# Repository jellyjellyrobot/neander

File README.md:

# Neander

The Neander is a microcontroller platform that is created for NUS Greyhats' X-CTF.

This board is based on the ESP8266 microcontroller series by Espressif and derives certain components from Adafruit's Feather and Sparkfun's Thing based on the same microcontroller platform.

## Specifications

- ESP8266 32 bit Microcontroller platform with Integrated 802.11 b/g/n
- Auto-Reset
- Deep Sleep option (enabled)
- 500mA 3.3V Voltage Regulator
- USB-Serial Interface (CP2102)
- 6 Buttons (including Reset)
- Lithium Polymer Charger
- Indicator LEDs (Charge, Power)
- Backlight LEDs and Switches

## Neander Accessory kit

The Neander comes with an accessory kit which includes the following

- Lithium Polymer Battery
- MicroUSB cable
- Short Lanyard (For CP2102)
- 10cm Dupont Jumper Cables (10 each: M-M, F-F, F-M)
- Single Row Headers 1*40 pin
- Double Row Headers 2*6 pin
- 6 Jumpers
- 2 Stickers

## Using the USB-Serial Adaptor

The on-board USB-Serial Adaptor is based on a Silabs CP2102 chip.

OS specific drivers can be found on the [manufacturer's website](http://www.silabs.com/products/mcu/Pages/USBtoUARTBridgeVCPDrivers.aspx). A tutorial on how to use this device can be found [here](https://learn.sparkfun.com/tutorials/cp2102-usb-to-serial-converter-hook-up-guide). The datasheet can be found [here](https://cdn.sparkfun.com/datasheets/BreakoutBoards/CP2102_v1.2.pdf).

## Interfacing with other electronics

The USB-Serial adaptor is supplied as a breakout board. If you need a serial adaptor "out in the field", you can choose to break it and solder on any 2.54mm compatible headers for convenience.

To interface the serial adaptor with other serial devices with the CP2102 in-situ, you may solder the double row headers found in the accessory packs and disconnect (desolder) all 5 SMD jumper pads.

## XCTF 2016

Here are the repositories for the [qualifiers] (https://github.com/NUSGreyhats/xctf-2016-quals-challenges) and [finals](https://github.com/NUSGreyhats/x-ctf-2016-finals).

## Contributors

Jacob  
Darell  
Yu Siang  
Jeremias

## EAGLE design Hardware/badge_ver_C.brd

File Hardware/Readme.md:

#Hardware

## Stages

This board was designed in 3 stages. 2 Prototypes were made (with mistakes :D) and the final board turned out pretty ok. Lucky us!

##Bill of Materials

The [Bill of Materials](https://docs.google.com/spreadsheets/d/1qAbk1U9EDFSMrGZ68tAHjeOSaGbgNGMX1J6-07fJV7c/edit?usp=sharing) can be found here!

## Production Writeups

Darell (@geekman) has produced a great writeup [here](http://irq5.io/2016/06/22/designing-the-x-ctf-2016-badge/)!

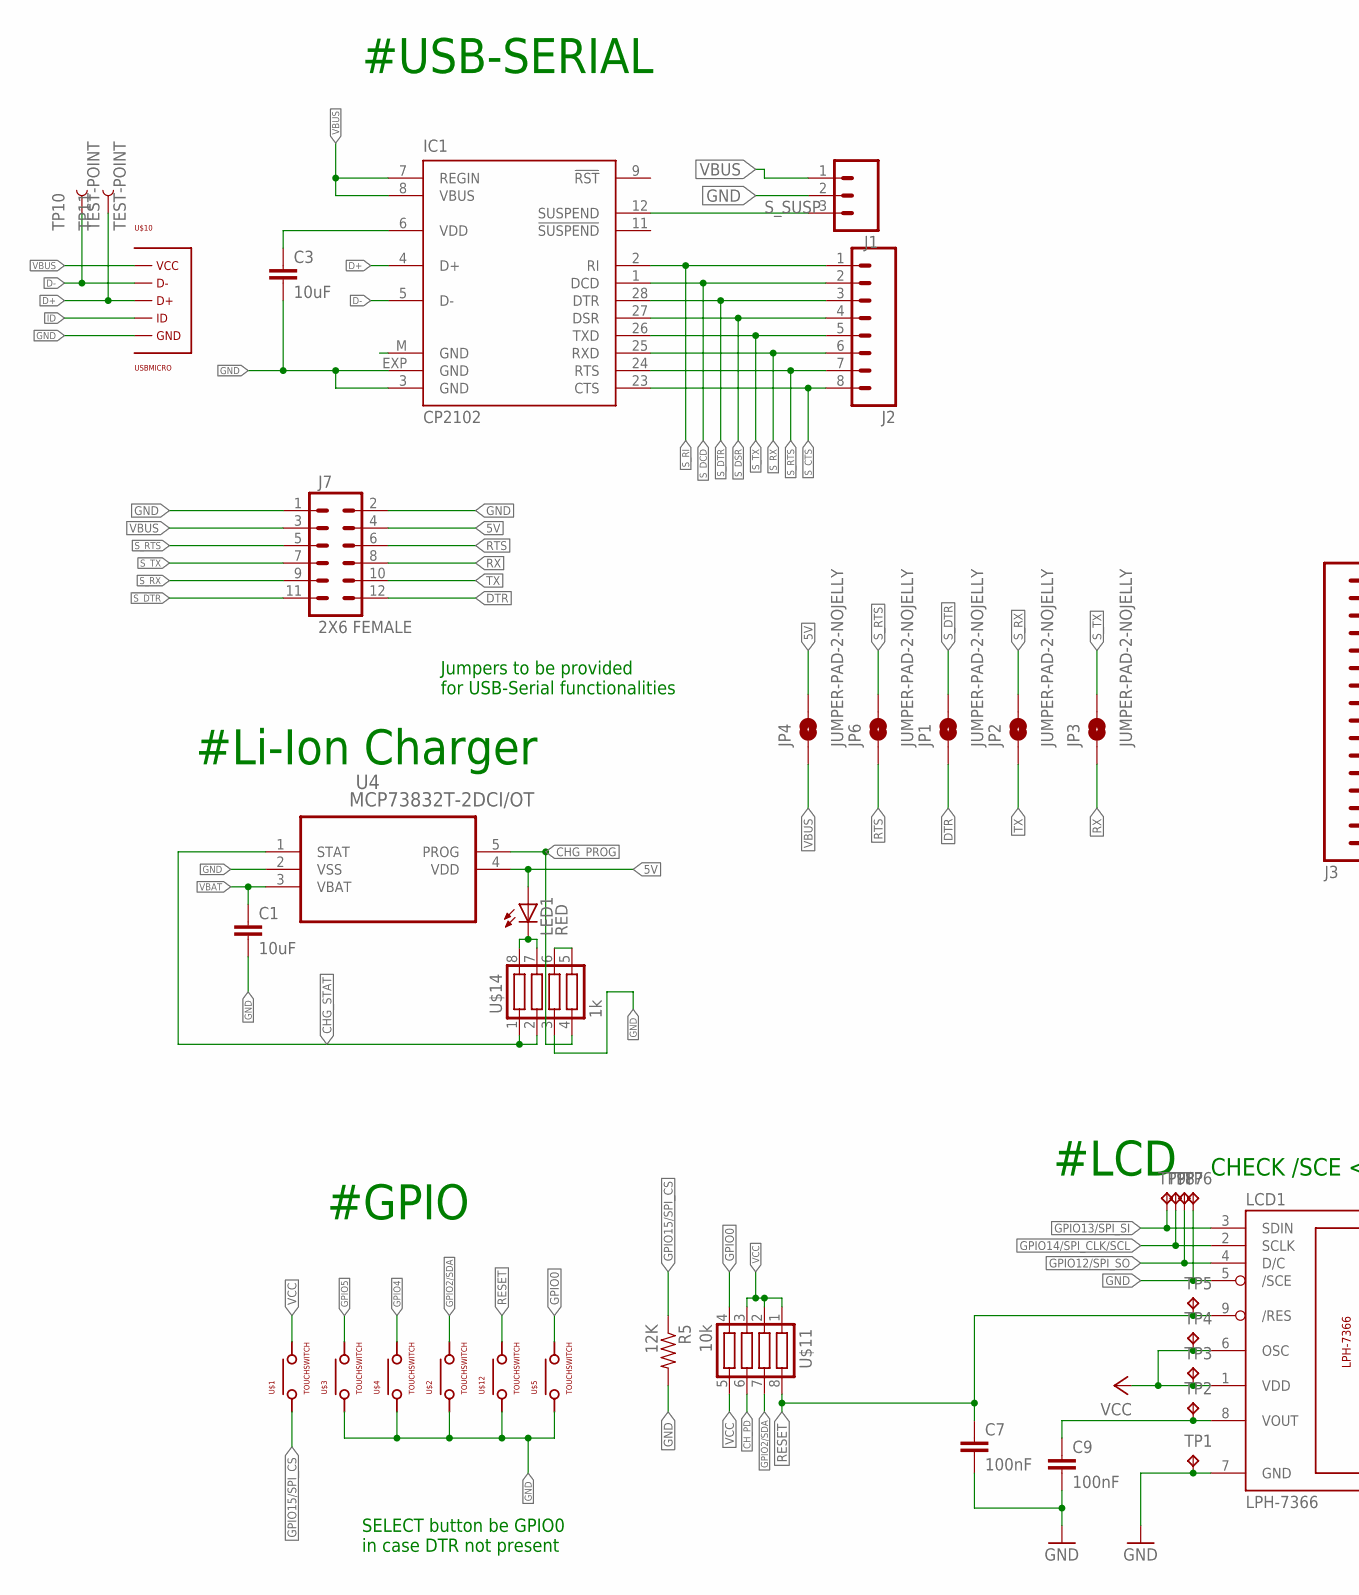
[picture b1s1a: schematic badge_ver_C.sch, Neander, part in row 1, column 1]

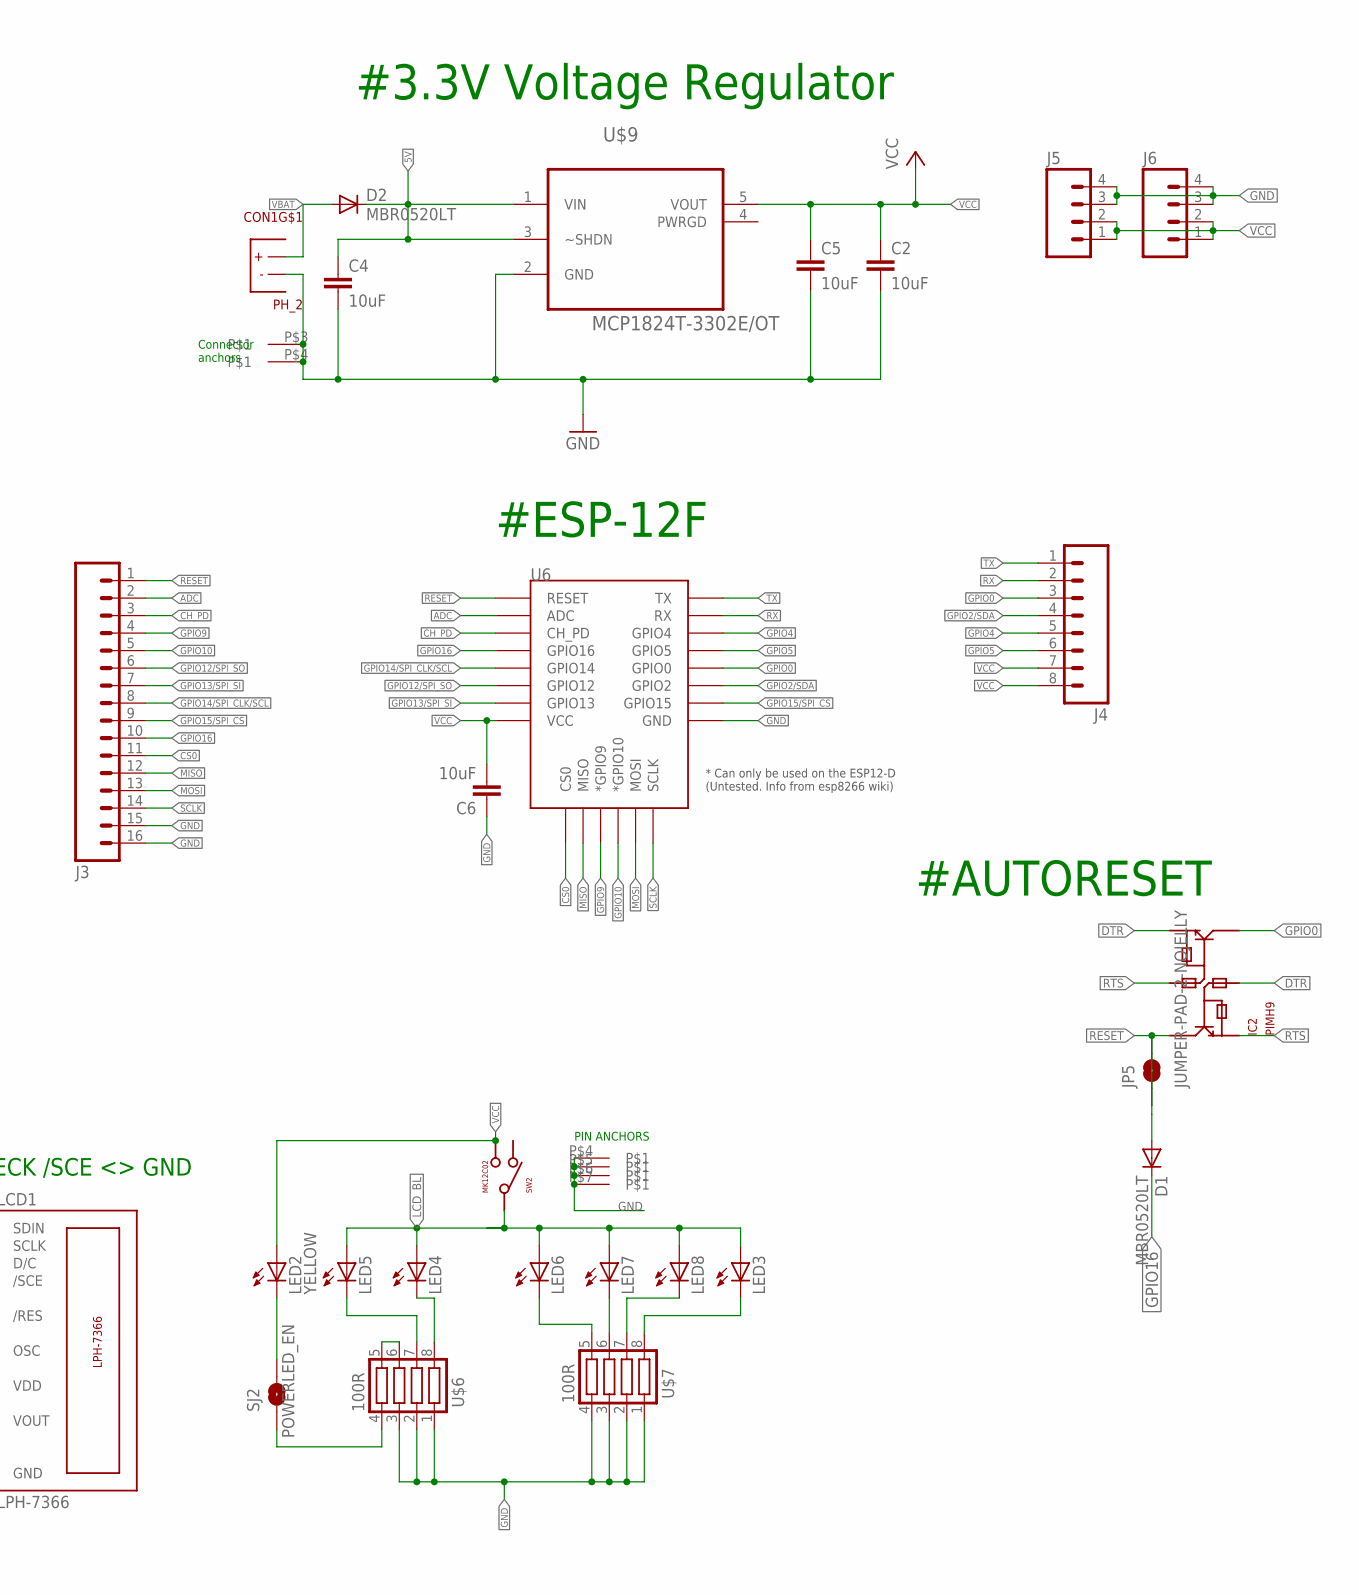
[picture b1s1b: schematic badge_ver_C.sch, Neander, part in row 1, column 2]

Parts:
C1, C2, C3, C4, C5, C6: 10uF; 0805-CAP
C7, C9: 100nF; 0805-CAP
CON1: PH_2
D1, D2: MBR0520LT; SOD123
IC1: CP2102; MLP28
IC2: PIMH9; SOT457
J1: M03PTH; 1X03
J2: M08SILK_FEMALE_PTH; 1X08
J3: M16PTH; 1X16
J4: M08; 1X08_ROUND
J5, J6: M04PTH; 1X04
J7: 2X6 FEMALE; 2X6
JP1, JP2, JP3, JP4, JP5, JP6: JUMPER-PAD-2-NOJELLY; JELLYPAD-JUMPER-2-NO_NO_SILK
LCD1: LPH-7366
LED1: RED; SML0805
LED2: YELLOW; SML0805
LED3, LED4, LED5, LED6, LED7, LED8: LEDSML0805; SML0805
R5: 12K; 0805
SJ2: POWERLED_EN; SJ_2S-TRACE
SW2: MK12C02
TP1, TP2, TP3, TP4, TP5, TP6, TP7, TP8, TP9: TPB1,27; B1,27
TP10, TP11: TEST-POINT; PAD.02X.02_JELLY
U4: MCP73832T-2DCI/OT; SOT95P300X145-5N
U6: ESP12ESMD; ESP12E-SMD
U$1, U$2, U$3, U$4, U$5, U$12: TOUCHSWITCH; EVQQWN03W
U$6, U$7: 100R; YC164
U$9: MCP1824T-3302E/OT; SOT95P270X145-5N
U$10: USBMICRO
U$11: 10k; YC164
U$14: 1k; YC164

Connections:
5V: C4.1, D2.C, J7.4, JP4.2, LED1.A, U4.4 (VDD), U$9.1 (VIN), U$9.3 (~SHDN)
ADC: J3.2, U6.ADC
CHG_PROG: U4.5 (PROG), U$14.4
CHG_STAT: U4.1 (STAT), U$14.1, U$14.2
CH_PD: J3.3, U6.CH_PD, U$11.6
CS0: J3.11, U6.CS0
D+: IC1.4 (D+), TP11.P$1, U$10.P$D+
D-: IC1.5 (D-), TP10.P$1, U$10.P$D-
DTR: IC2.P$2, IC2.P$4, J7.12, JP1.1
GND: C1.2, C2.2, C3.2, C4.2, C5.2, C6.1, C7.2, C9.2, CON1.P$1, CON1.P$3, CON1.P$4, IC1.3 (GND), IC1.EXP (GND), J1.2, J3.15, J3.16, J5.3, J5.4, J6.3, J6.4, J7.1, J7.2, LCD1.5 (/SCE), LCD1.7 (GND), R5.2, SW2.P$4, SW2.P$5, SW2.P$6, SW2.P$7, TP1.TP, TP6.TP, U4.2 (VSS), U6.GND, U$2.P$1, U$2.P$4, U$3.P$1, U$3.P$4, U$4.P$1, U$4.P$4, U$5.P$1, U$5.P$4, U$6.1, U$6.2, U$6.3, U$7.1, U$7.2, U$7.3, U$7.4, U$9.2 (GND), U$10.P$GND, U$12.P$1, U$12.P$4, U$14.3
GPIO0: IC2.P$3, J4.3, U6.GPIO0, U$5.P$2, U$5.P$3, U$11.4
GPIO2/SDA: J4.4, U6.GPIO2, U$2.P$2, U$2.P$3, U$11.7
GPIO4: J4.5, U6.GPIO4, U$4.P$2, U$4.P$3
GPIO5: J4.6, U6.GPIO5, U$3.P$2, U$3.P$3
GPIO9: J3.4, U6.GPIO9 (*GPIO9)
GPIO10: J3.5, U6.GPIO10 (*GPIO10)
GPIO12/SPI_SO: J3.6, LCD1.4 (D/C), TP7.TP, U6.GPIO12
GPIO13/SPI_SI: J3.7, LCD1.3 (SDIN), TP9.TP, U6.GPIO13
GPIO14/SPI_CLK/SCL: J3.8, LCD1.2 (SCLK), TP8.TP, U6.GPIO14
GPIO15/SPI_CS: J3.9, R5.1, U6.GPIO15, U$1.P$1, U$1.P$4
GPIO16: D1.C, J3.10, U6.GPIO16
ID: U$10.P$ID
LCD_BL: LED3.A, LED4.A, LED5.A, LED6.A, LED7.A, LED8.A, SW2.P$2
MISO: J3.12, U6.MISO
MOSI: J3.13, U6.MOSI
unnamed: LED1.C, U$14.7, U$14.8
unnamed: U$14.5, U$14.6
unnamed: LED7.C, U$7.6
unnamed: LED8.C, U$7.7
unnamed: C9.1, LCD1.8 (VOUT), TP2.TP
unnamed: U$6.5, U$6.6
unnamed: LED4.C, U$6.8
unnamed: LED5.C, U$6.7
unnamed: LED3.C, U$7.8
unnamed: SJ2.1, U$6.4
unnamed: LED2.C, SJ2.2
unnamed: C3.1, IC1.6 (VDD)
unnamed: LED6.C, U$7.5
RESET: C7.1, D1.A, IC2.P$6, J3.1, JP5.1, JP5.2, LCD1.9 (/RES), TP5.TP, U6.RESET, U$11.8, U$12.P$2, U$12.P$3
RTS: IC2.P$1, IC2.P$5, J7.6, JP6.1
RX: J4.2, J7.8, JP3.1, U6.RXD0 (RX)
SCLK: J3.14, U6.SCLK
S_CTS: IC1.23 (CTS), J2.8
S_DCD: IC1.1 (DCD), J2.2
S_DSR: IC1.27 (DSR), J2.4
S_DTR: IC1.28 (DTR), J2.3, J7.11, JP1.2
S_RI: IC1.2 (RI), J2.1
S_RTS: IC1.24 (RTS), J2.7, J7.5, JP6.2
S_RX: IC1.25 (RXD), J2.6, J7.9, JP2.2
S_SUSP: IC1.12 (SUSPEND), J1.3
S_TX: IC1.26 (TXD), J2.5, J7.7, JP3.2
TX: J4.1, J7.10, JP2.1, U6.TXD0 (TX)
VBAT: C1.1, CON1.P$2, D2.A, U4.3 (VBAT)
VBUS: IC1.7 (REGIN), IC1.8 (VBUS), J1.1, J7.3, JP4.1, U$10.P$VCC
VCC: C2.1, C5.1, C6.2, J4.7, J4.8, J5.1, J5.2, J6.1, J6.2, LCD1.1 (VDD), LCD1.6 (OSC), LED2.A, SW2.P$3, TP3.TP, TP4.TP, U6.VCC, U$1.P$2, U$1.P$3, U$9.5 (VOUT), U$11.1, U$11.2, U$11.3, U$11.5

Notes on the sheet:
SELECT button be GPIO0 in case DTR not present
#LCD
#Li-Ion Charger
#3.3V Voltage Regulator
#USB-SERIAL
#GPIO
#AUTORESET
#ESP-12F
Jumpers to be provided for USB-Serial functionalities
CHECK /SCE <> GND
Connector anchors
PIN ANCHORS

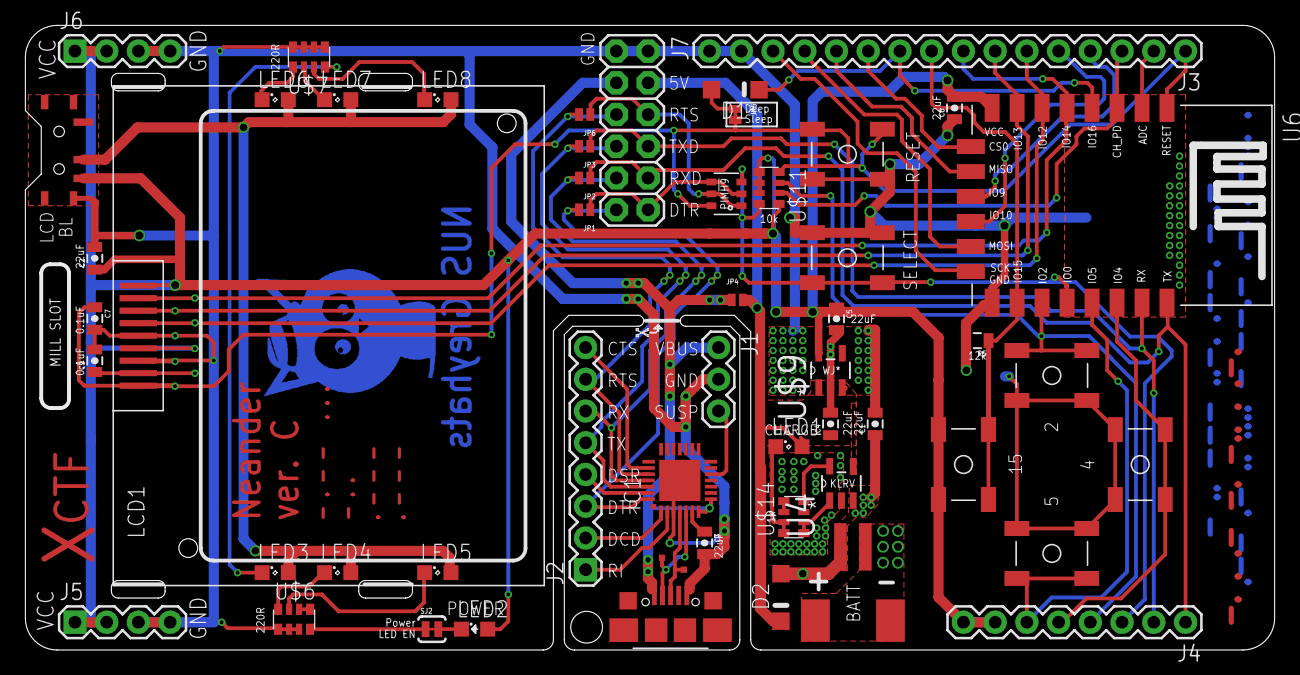
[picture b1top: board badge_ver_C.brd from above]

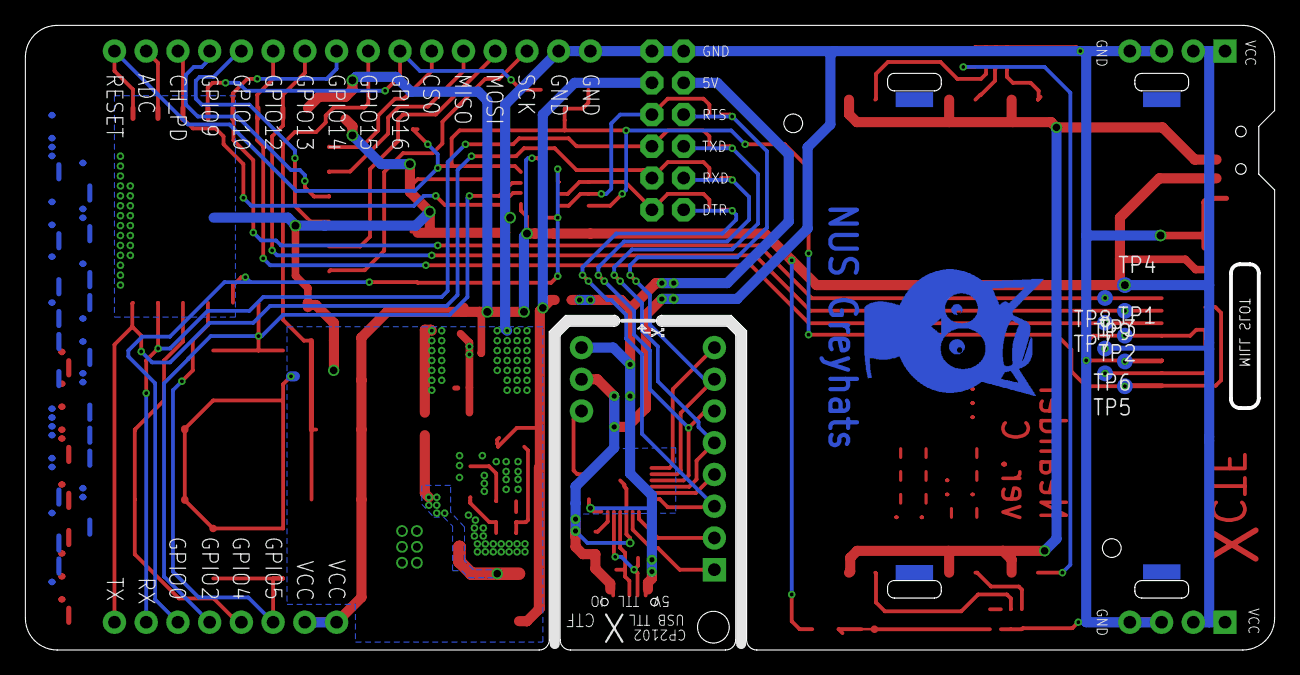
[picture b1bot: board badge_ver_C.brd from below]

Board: 2 copper layers, 99.8 x 49.8 mm, 63 parts (9 on the bottom side), 54 nets.

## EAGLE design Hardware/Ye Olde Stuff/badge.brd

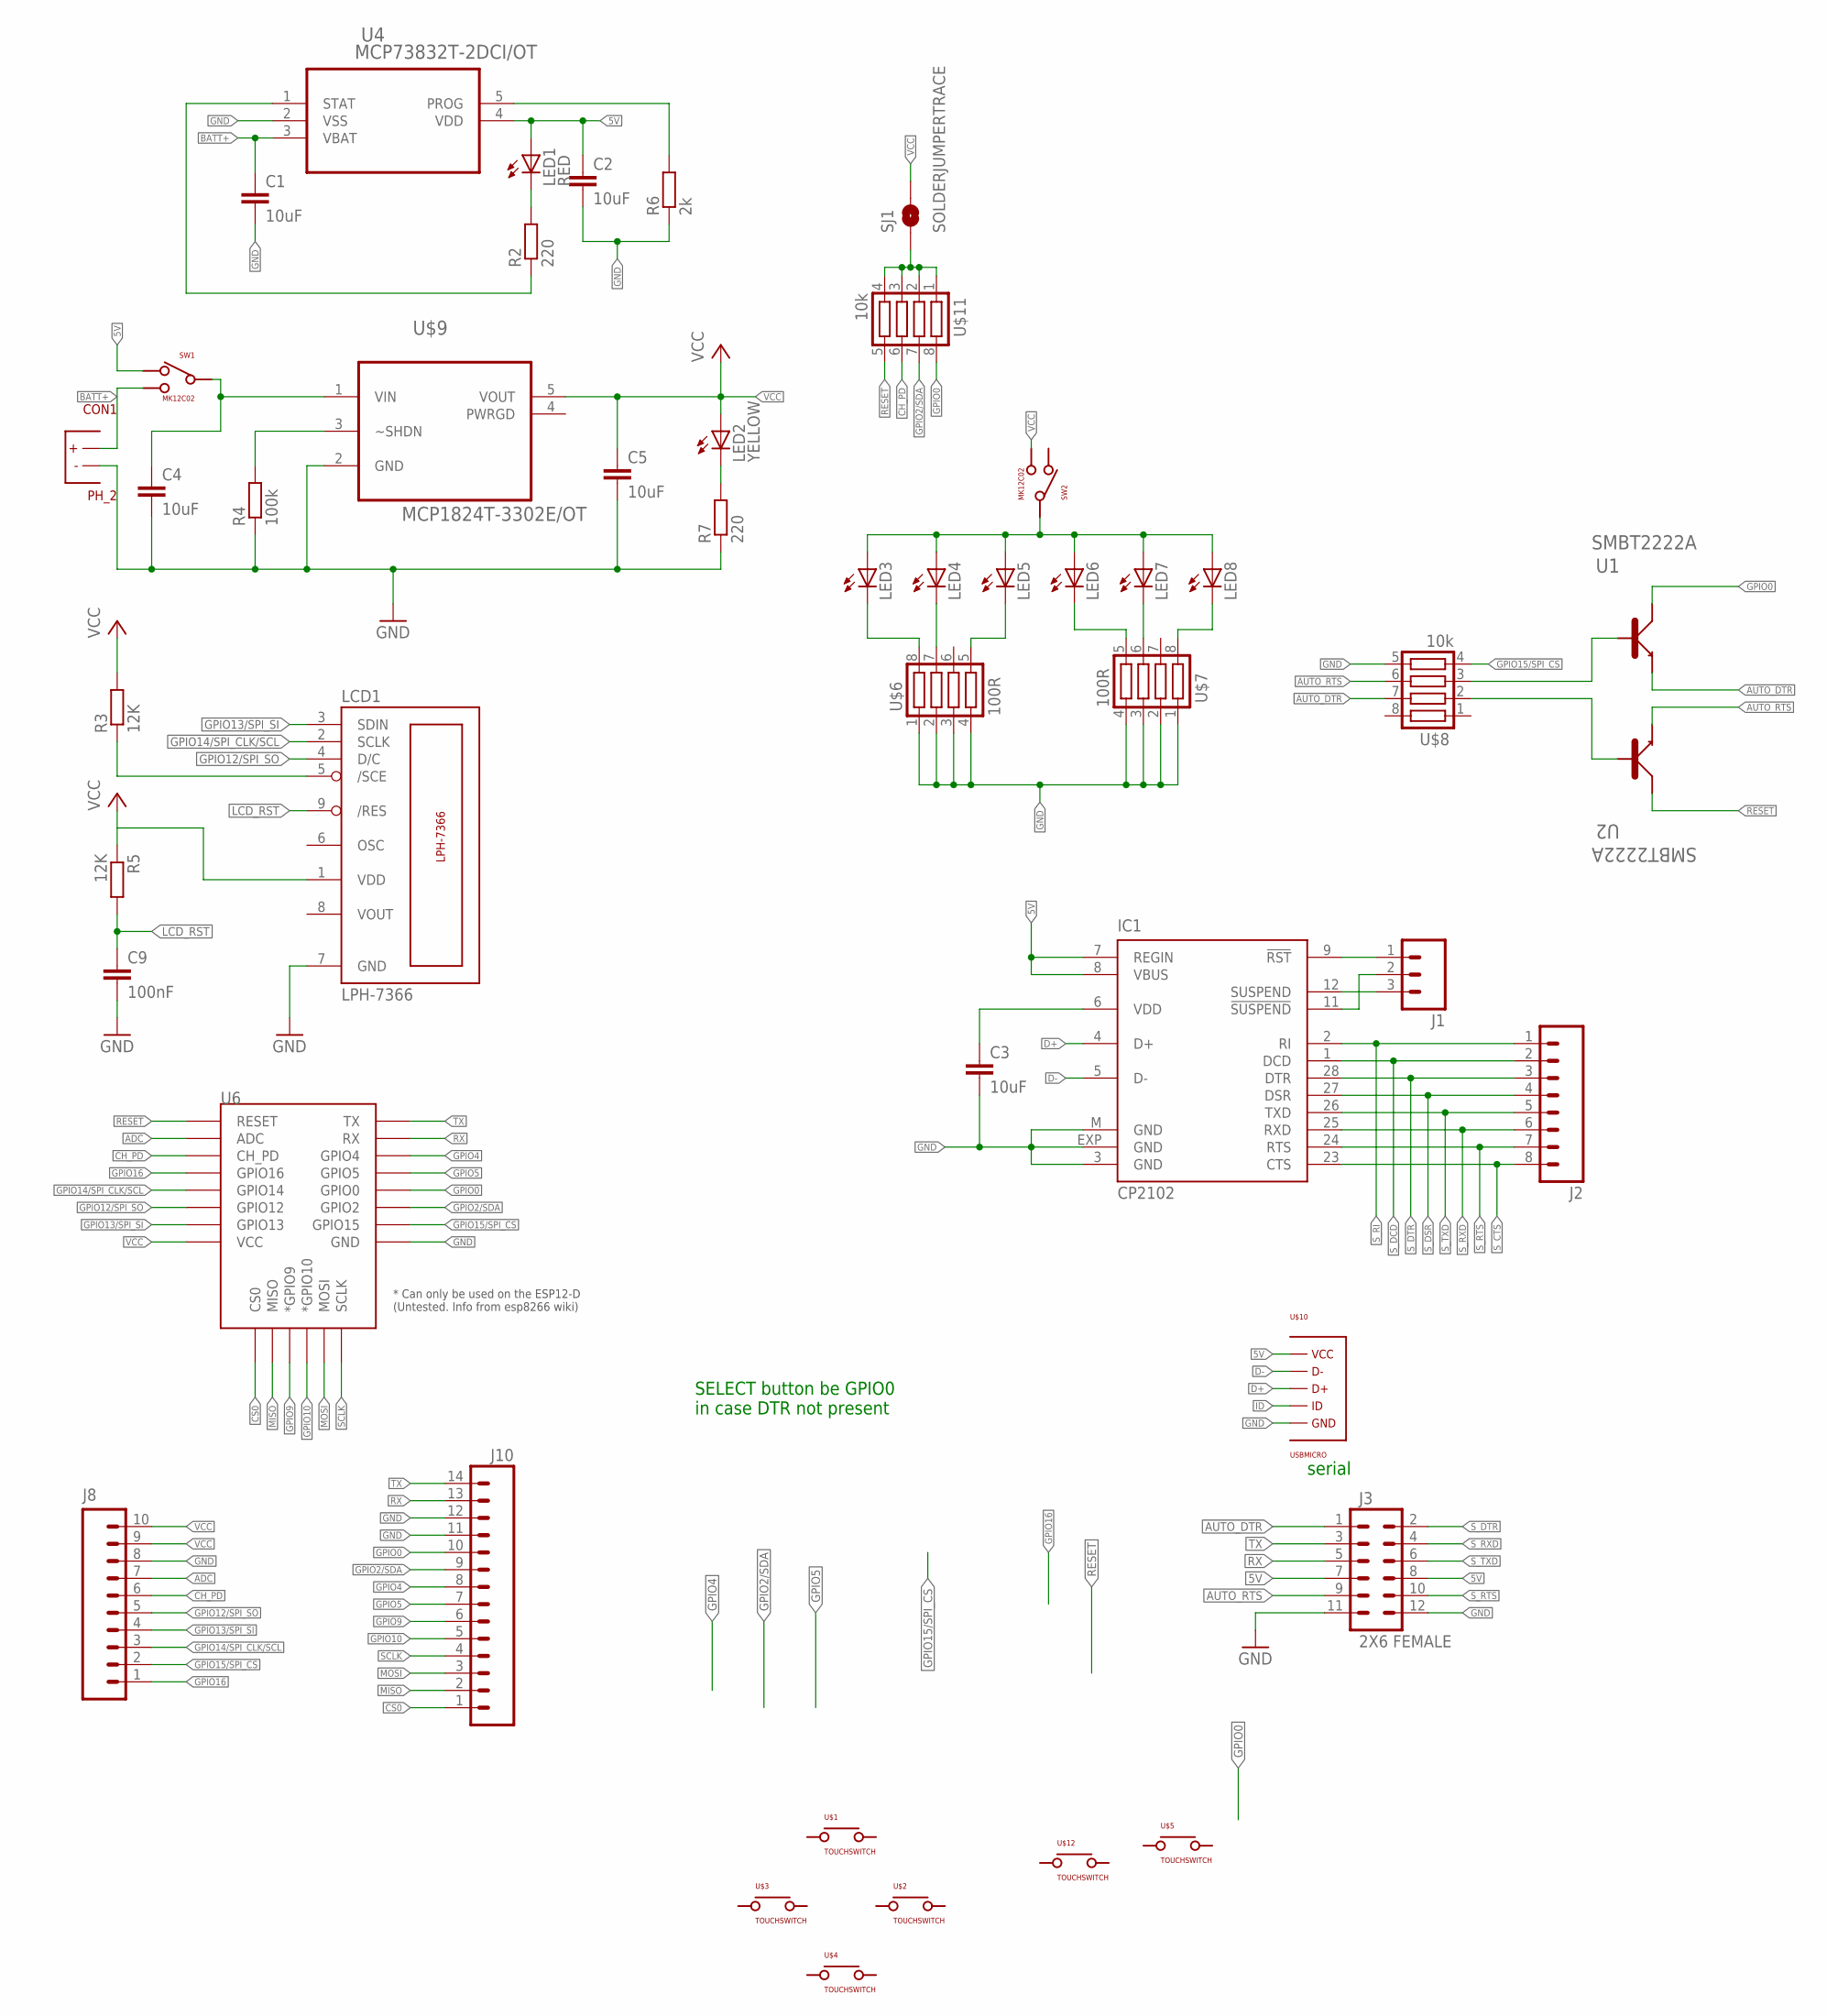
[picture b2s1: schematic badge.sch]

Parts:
C1, C2, C3, C4, C5: 10uF; C0603K
C9: 100nF; C0603K
CON1: PH_2
IC1: CP2102; MLP28
J1: M03PTH; 1X03
J2: M08SILK_FEMALE_PTH; 1X08
J3: 2X6 FEMALE; 2X6
J8: M10SILK_FEMALE_PTH; 1X10
J10: M14; 1X14
LCD1: LPH-7366
LED1: RED; SML0805
LED2: YELLOW; SML0805
LED3, LED4, LED5, LED6, LED7, LED8: LEDSML0805; SML0805
R2, R7: 220; R0603W
R3, R5: 12K; R0603W
R4: 100k; R0603W
R6: 2k; R0603W
SJ1: SOLDERJUMPERTRACE; SJ_2S-TRACE
SW1, SW2: MK12C02
U1, U2: SMBT2222A; SOT95P290X110-3N
U4: MCP73832T-2DCI/OT; SOT95P300X145-5N
U6: ESP12ESMD; ESP12E-SMD
U$1, U$2, U$3, U$4, U$5, U$12: TOUCHSWITCH; EVQQWN03W
U$6, U$7: 100R; YC164
U$8, U$11: 10k; YC164
U$9: MCP1824T-3302E/OT; SOT95P270X145-5N
U$10: USBMICRO

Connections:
5V: C2.1, IC1.7 (REGIN), IC1.8 (VBUS), J3.7, J3.8, LED1.A, SW1.P$2, U4.4 (VDD), U$10.P$VCC
ADC: J8.7, U6.ADC
AUTO_DTR: J3.1, U1.2 (E), U$8.7
AUTO_RTS: J3.9, U2.2 (E), U$8.6
BATT+: C1.1, CON1.P$2, SW1.P$3, U4.3 (VBAT)
CH_PD: J8.6, U6.CH_PD, U$11.6
CS0: J10.1, U6.CS0
D+: IC1.4 (D+), U$10.P$D+
D-: IC1.5 (D-), U$10.P$D-
GND: C1.2, C2.2, C3.2, C4.2, C5.2, C9.2, CON1.P$1, IC1.3 (GND), IC1.EXP (GND), IC1.M (GND), J3.11, J3.12, J8.8, J10.11, J10.12, LCD1.7 (GND), R4.1, R6.1, R7.1, U4.2 (VSS), U6.GND, U$6.1, U$6.2, U$6.3, U$6.4, U$7.1, U$7.2, U$7.3, U$7.4, U$8.5, U$9.2 (GND), U$10.P$GND
GPIO0: J10.10, U1.3 (C), U6.GPIO0, U$11.8
GPIO2/SDA: J10.9, U6.GPIO2, U$11.7
GPIO4: J10.8, U6.GPIO4
GPIO5: J10.7, U6.GPIO5
GPIO9: J10.6, U6.GPIO9 (*GPIO9)
GPIO10: J10.5, U6.GPIO10 (*GPIO10)
GPIO12/SPI_SO: J8.5, LCD1.4 (D/C), U6.GPIO12
GPIO13/SPI_SI: J8.4, LCD1.3 (SDIN), U6.GPIO13
GPIO14/SPI_CLK/SCL: J8.3, LCD1.2 (SCLK), U6.GPIO14
GPIO15/SPI_CS: J8.2, U6.GPIO15, U$8.4
GPIO16: J8.1, U6.GPIO16
ID: U$10.P$ID
LCD_RST: C9.1, LCD1.9 (/RES), R5.2
MISO: J10.2, U6.MISO
MOSI: J10.3, U6.MOSI
unnamed: C4.1, SW1.P$1, U$9.1 (VIN)
unnamed: LED3.A, LED4.A, LED5.A, LED6.A, LED7.A, LED8.A, SW2.P$1
unnamed: LCD1.5 (/SCE), R3.1
unnamed: R4.2, U$9.3 (~SHDN)
unnamed: SJ1.1, U$11.1, U$11.2, U$11.3, U$11.4
unnamed: R6.2, U4.5 (PROG)
unnamed: LED2.C, R7.2
unnamed: LED7.C, U$7.6
unnamed: LED1.C, R2.2
unnamed: R2.1, U4.1 (STAT)
unnamed: LED3.C, U$6.8
unnamed: LED4.C, U$6.7
unnamed: LED5.C, U$6.5
unnamed: U1.1 (B), U$8.3
unnamed: IC1.11 (!SUSPEND), J1.2
unnamed: IC1.12 (SUSPEND), J1.3
unnamed: U2.1 (B), U$8.2
unnamed: IC1.9 (!RST), J1.1
unnamed: C3.1, IC1.6 (VDD)
unnamed: LED6.C, U$7.5
unnamed: LED8.C, U$7.8
RESET: U2.3 (C), U6.RESET, U$11.5
RX: J3.5, J10.13, U6.RXD0 (RX)
SCLK: J10.4, U6.SCLK
S_CTS: IC1.23 (CTS), J2.8
S_DCD: IC1.1 (DCD), J2.2
S_DSR: IC1.27 (DSR), J2.4
S_DTR: IC1.28 (DTR), J2.3, J3.2
S_RI: IC1.2 (RI), J2.1
S_RTS: IC1.24 (RTS), J2.7, J3.10
S_RXD: IC1.25 (RXD), J2.6, J3.4
S_TXD: IC1.26 (TXD), J2.5, J3.6
TX: J3.3, J10.14, U6.TXD0 (TX)
VCC: C5.1, J8.9, J8.10, LCD1.1 (VDD), LED2.A, R3.2, R5.1, SJ1.2, SW2.P$3, U6.VCC, U$9.5 (VOUT)

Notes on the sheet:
serial
SELECT button be GPIO0 in case DTR not present

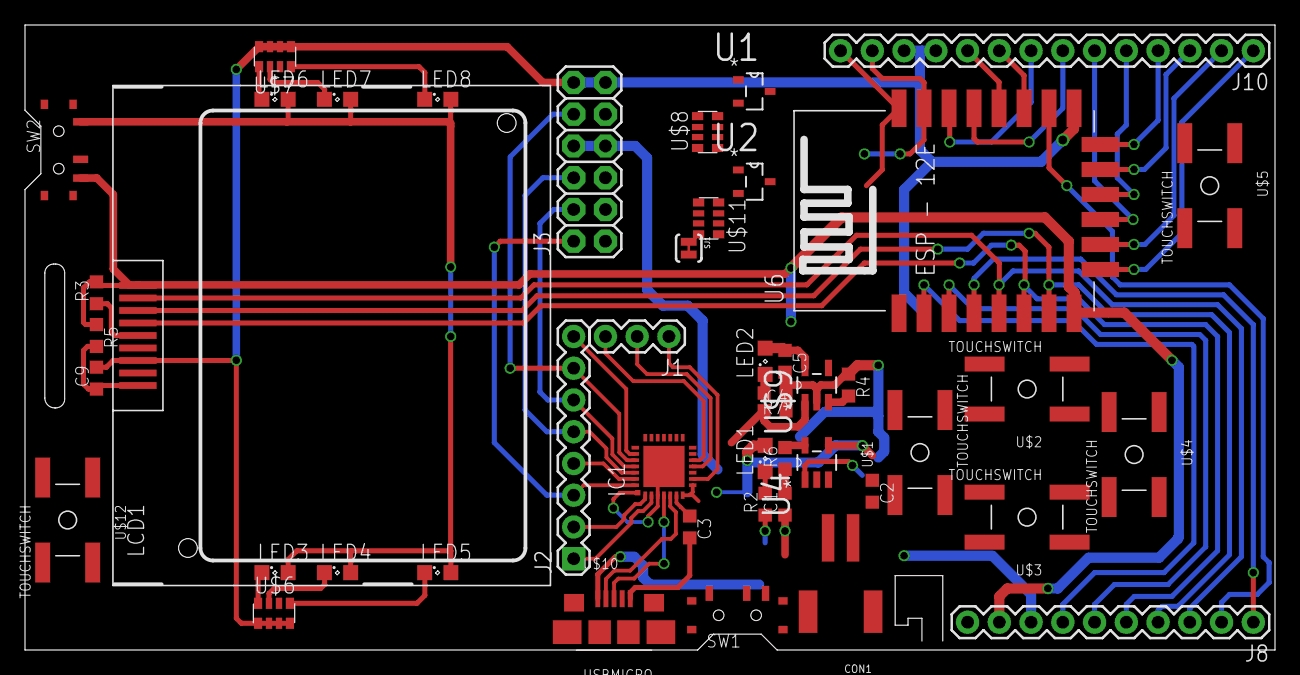
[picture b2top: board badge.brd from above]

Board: 2 copper layers, 100.0 x 50.0 mm, 47 parts (0 on the bottom side), 58 nets.

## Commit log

2016-03-10 init
2016-03-13 for ys
2016-03-18 switching over to ESP-12e/f
2016-03-21 before the big change
2016-03-22 before cp2102
2016-03-22 the change cometh
2016-03-23 before addition of autoreset
2016-03-24 Preliminary Neander v0.0
2016-03-24 changed readme
2016-03-24 forgot one name
2016-03-24 Schematic: LDO !shdn is to be high, not low
2016-03-25 Redid a lot of stuff, added silks.
2016-03-25 Fixed the files places
2016-03-25 Moved power LED, sharing the r-net for the backlight
2016-03-25 DTR and RTS silks on jumper header were swapped
2016-03-25 Swapped a silks, added more silks, bit of routing changes
2016-03-25 Moved a bit of stuff to prevent stop-mask errors, and one dimension error
2016-03-25 added some changes from YS
2016-03-25 Paralleled GND trace, rerouted reset trace for wider separation
2016-03-25 deleted lone component
2016-03-25 Fixed odd shaped reset trace at reset button
2016-03-25 Minimal nonessential changes
2016-03-26 moved res array U to away from RESET button
2016-03-26 rectified errors in ERC, DRC
2016-03-26 routed LED traces away from LCD mounting holes, prevent short between USB case and VBUS
2016-03-26 Added snapoffable USB-serial
2016-03-26 One cap's silk got mangled in the cut path
2016-03-26 Bit more heatsinking for the battery charger
2016-03-26 Fixed some silk and mask errors
2016-03-26 Minor changes
2016-03-26 Added SJ2 for power LED for reducing power usage
2016-03-26 Rerouted and labeled some nets
2016-03-27 Replaced 2 resistors with 1 r-net.
2016-03-27 Added IO16 <-> Reset; Added mounting holes for LCD; Removed notice for Cutout
2016-03-27 added logo, names
2016-03-27 made logo shiny
2016-03-27 Repositioned vias, added stop mask for LCD mounts
2016-03-27 Moved text to bplace
2016-03-28 removed DS_stores; update .gitignore
2016-03-28 before teardown
2016-03-28 moved ESP to the opposite end w.r.t. LCD
2016-03-28 Added !susp to serial headers. Rerouted many traces
2016-03-28 Rerouted stuff. Added new power supply headers near LCD
2016-03-28 May not have saved for last commit
2016-03-28 fixed XCTF solder mask
2016-03-28 Fixed most of the errors, optimized some traces
2016-03-28 added decoup cap; antenna gnd plane; minor edits;
2016-03-28 added text to bottom layer; mitred edges;
2016-03-28 inverted text right way round
2016-03-29 Edited silkscreen alignments and remove redundant silkscreen markings
2016-03-29 changed morse text
2016-03-29 migrated all caps to 0805
2016-04-08 add skeleton for firmware
2016-05-08 updated board schematics and placement
2016-05-09 added testpoints; converted name into pads
2016-05-09 Replaced LCD footprint and adjusted nearby traces. New footprint has wider mounting holes and slightly thinner mating connector traces. Also removed a stop mask placed over the connector.
2016-05-09 Connect GPIO16 to RESET via diode to enable deep sleep.
2016-05-09 Added auto-switch between battery & USB power, just like Huzzah. Removed the need for switch SW1. Since lipo charger output is now the same as regulator input, and C2 & C4 were next to each other, C2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
2016-05-09 Moved UP button away from LiPo connector; too close
2016-05-09 added top mask for LCD pads
2016-05-10 increased separation between buttons and battery connector; made morse code into pads; edited text descriptions
2016-05-10 Added cathode markings for D1 & D2.
2016-05-19 Fixed transistor layout; Repositioned LCD caps; added 10uF cap to LCD for Brownouts; Increased width of custom layouts; Unbridged 5v; Changed name to FeTChX; ref C; Encoded names; Changed XCTF logo w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
2016-05-19 named changed back to neander
2016-05-19 edits as suggested by YS
2016-05-19 fixed a small via
2016-05-19 Added optional connections to the anchors for the battery connector and slide switch To place on schematic, use the invoke tool
2016-05-19 removed slant from lcd reset trace upon Yu Siang's rec
2016-05-19 increased power trace width
2016-05-20 Added test points for USB data lines.
2016-05-20 Adjusted LCD mounting holes further apart for snug fit.
2016-05-20 Shortened the exposed SMD pads for ESP12-E. They are wayyy too long, just like the tact switches used to be.
2016-05-20 Moved buttons and ESP12E to the right, spaced out.
2016-05-20 Increased ground fills isolation to avoid manufacturing problems.
2016-05-20 Replaced serial jumpers with a header. Thus removing the need to populate the jumpers during board assembly.
2016-05-21 Removed 12K resistor after connecting LCD & ESP resets.
2016-05-21 electrons fell out
2016-05-21 Added Eagle library containing LCD package.
2016-05-21 moved pads and vias out of the way
2016-05-21 dunno what I did
2016-05-21 okey dokey
2016-05-21 Fixed VBUS short-circuit overlap on CP2102 breakout
2016-05-21 All text back to vector for CAM, minor edits to some routing
2016-05-21 Routing optimizations Less contorted traces Making use of unused space for routing
2016-05-21 Added deep-sleep jumper point (closed by default); More routing optimizations
2016-05-21 Expanded the power supply area upwards, made all caps same dir
2016-05-21 Missing sch file from last commit!
2016-05-21 electrons still dropped out for some strange reason
2016-05-23 made slot wider for lanyard
2016-05-23 removed paste from test pads (USB D-/+)
2016-05-23 updated placements of text, job file
2016-05-24 updated for firmware compilation
2016-05-24 added test source files, updated main readme
2016-05-24 corrected minor error on main README
2016-05-24 minor edits, added image
2016-05-24 corrected spelling mistakes
2016-05-24 added readme for firmware
2016-05-24 added wiki
2016-05-24 minor corrections
2016-05-24 Rename GreyHat's to Greyhats' and added double space to insert line-breaks in credits
2016-05-24 Added dash between X and CTF
2016-06-03 add printout script
2016-06-03 resized logos
2016-06-03 added spaces between logos
2016-07-28 Added Readme.md for hardware
2016-07-28 Updated BOM
2016-07-28 Added link to competition firmware
2016-07-28 Add firmware writeup redirection

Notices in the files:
parts and their libraries:
SparkFun-Connectors: Licensing: Creative Commons ShareAlike 4.0 International - https://creativecommons.org/licenses/by-sa/4.0
